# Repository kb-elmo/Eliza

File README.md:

# Eliza

[![CC BY-NC-SA 4.0][cc-by-nc-sa-shield]][cc-by-nc-sa]

### A seamless, gasketmounted 12u 40% alice-style ergo keyboard

<!---->

### This board is still in the testing prototype phase. 
#### Use the files at your own risk.

---

[STEP files for the case](case/)

[KiCAD PCB files](pcb/)

[Gerbers for PCB production](pcb/gerbers/)

[JLCPCB BOM](pcb/fab/Eliza_bom_jlc.csv)

[JLCPCB CPL](pcb/fab/Eliza_cpl_jlc.csv)

[Vial-QMK firmware](firmware/)

---

This work is licensed under a
[Creative Commons Attribution-NonCommercial-ShareAlike 4.0 International License][cc-by-nc-sa].

[![CC BY-NC-SA 4.0][cc-by-nc-sa-image]][cc-by-nc-sa]

[cc-by-nc-sa]: http://creativecommons.org/licenses/by-nc-sa/4.0/
[cc-by-nc-sa-image]: https://licensebuttons.net/l/by-nc-sa/4.0/88x31.png
[cc-by-nc-sa-shield]: https://img.shields.io/badge/License-CC%20BY--NC--SA%204.0-lightgrey.svg

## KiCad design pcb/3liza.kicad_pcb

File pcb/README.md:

# Eliza PCB

### Features

- Powered by an Atmega32u2
- Basic ESD and overvoltage protection
- Centered USB type-C port for a detachable cable
- Fully programmable using [QMK](https://qmk.fm) and [Vial](https://get.vial.today)

---

### Supported layouts

---

### Preview

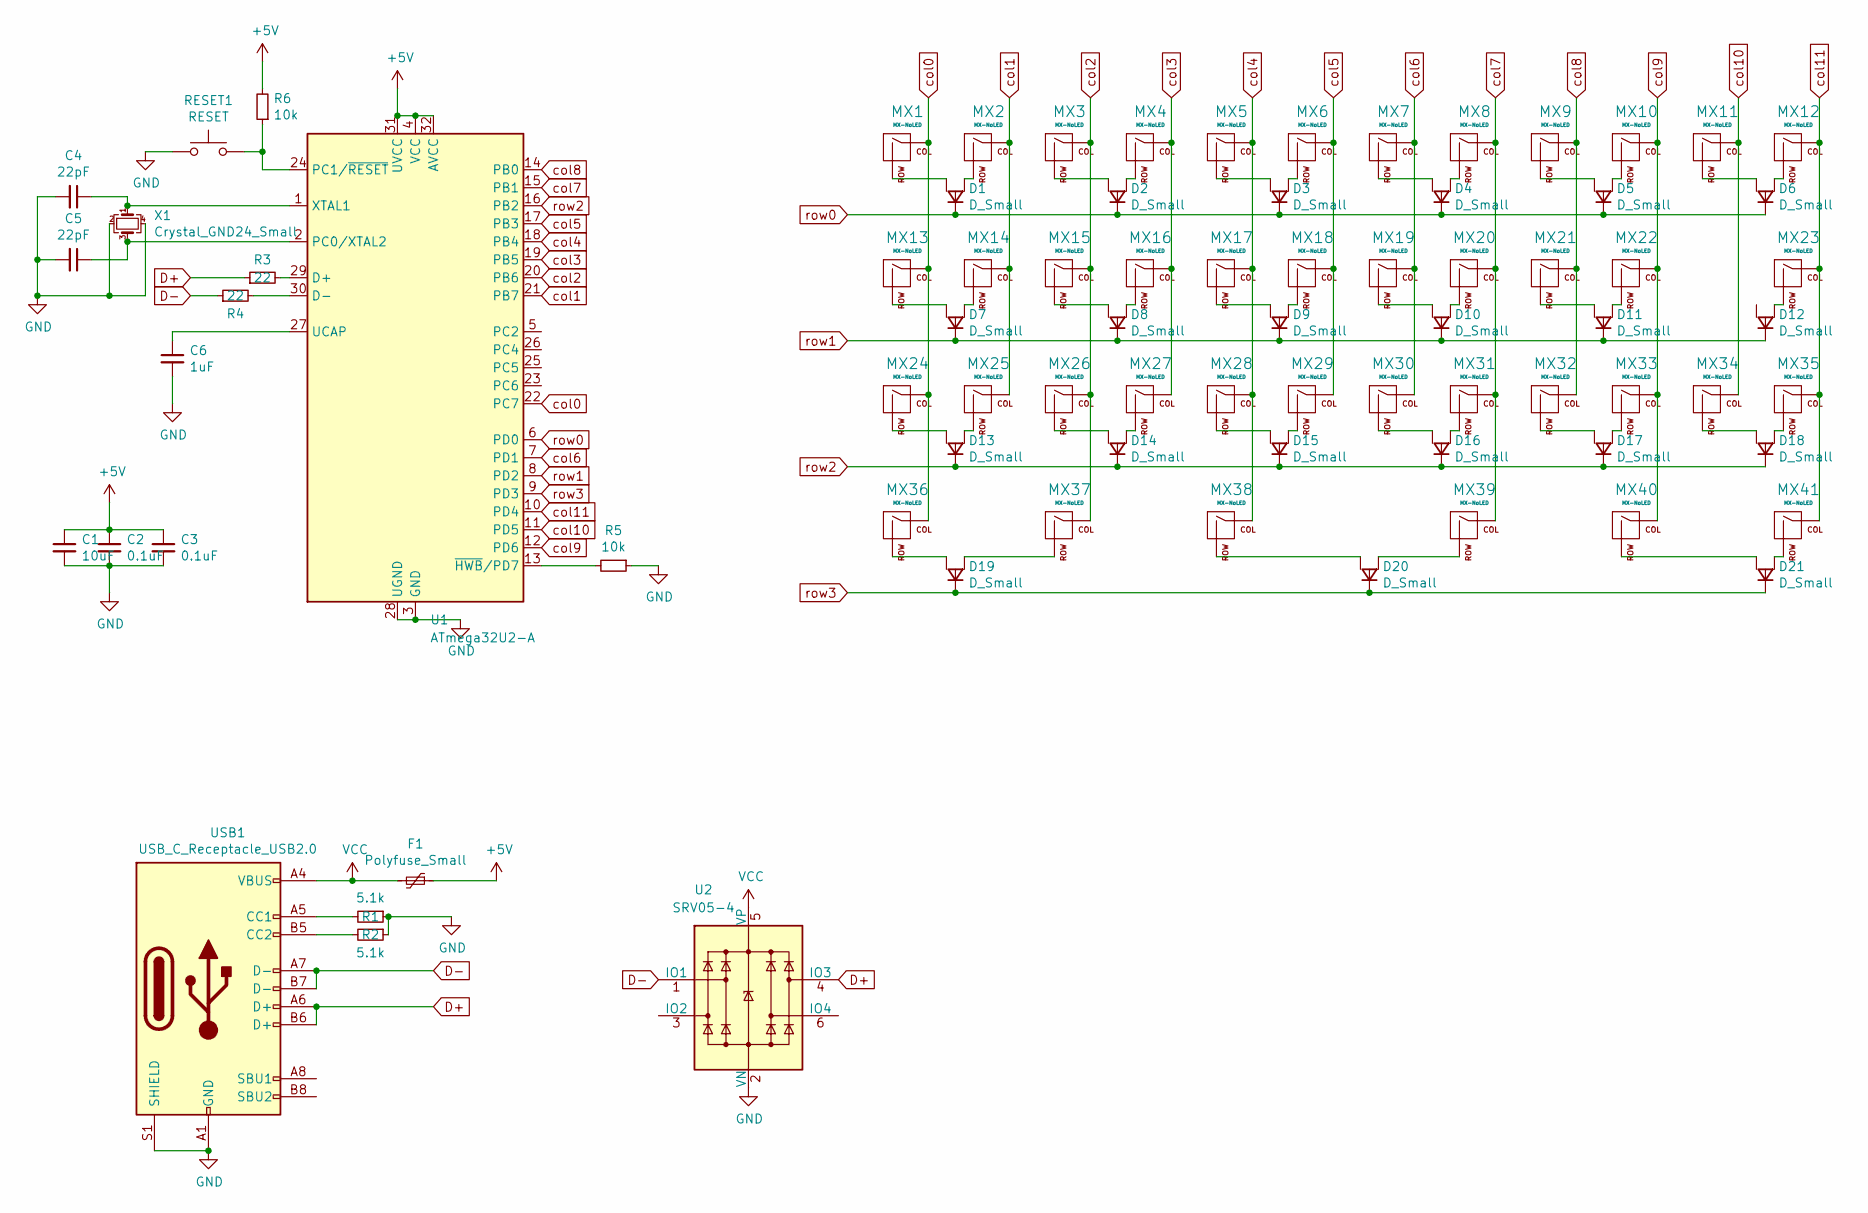
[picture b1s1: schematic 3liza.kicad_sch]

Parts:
C1: 10uF; C_0805_2012Metric; LCSC C91245
C2, C3: 0.1uF; C_0805_2012Metric; LCSC C49678
C4, C5: 22pF; C_0805_2012Metric; LCSC C1804
C6: 1uF; C_0805_2012Metric; LCSC C24123
D1, D2, D3, D4, D5, D6, D7, D8, D9, D10, D11, D12, D13, D14, D15, D16, D17, D18, D19, D20, D21: D_Small; D_SOT-23_ANK_norm; LCSC C68978
F1: Polyfuse_Small; Fuse_1206_3216Metric; LCSC C69688
MX1, MX2, MX3, MX4, MX5, MX6, MX7, MX8, MX9, MX10, MX11, MX12, MX13, MX14, MX15, MX16, MX17, MX18, MX19, MX20, MX21, MX22, MX23, MX24, MX25, MX26, MX27, MX28, MX29, MX30, MX31, MX32, MX33, MX34, MX35, MX36, MX37, MX40, MX41: MX-NoLED; MXOnly-1U-NoLED
MX38: MX-NoLED; MXOnly-2.75U-ReversedStabilizers-NoLED
MX39: MX-NoLED; MXOnly-2.25U-ReversedStabilizers-NoLED
R1, R2: 5.1k; R_0805_2012Metric; LCSC C27834
R3, R4: 22; R_0805_2012Metric; LCSC C17561
R5, R6: 10k; R_0805_2012Metric; LCSC C17414
RESET1: RESET; PinHeader_1x02_P2.54mm_Vertical
U1: ATmega32U2-A; TQFP-32_7x7mm_P0.8mm; LCSC C618733
U2: SRV05-4; SOT-23-6; LCSC C85364
USB1: USB_C_Receptacle_USB2.0; USB_C_Receptacle_HRO_TYPE-C-31-M-12; LCSC C165948
X1: Crystal_GND24_Small; Crystal_SMD_3225-4Pin_3.2x2.5mm; LCSC C13738

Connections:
+5V: C1.1, C2.1, C3.1, F1.1, R6.2, U1.4 (VCC), U1.31 (UVCC), U1.32 (AVCC)
D+: R3.1, U2.4 (IO3), USB1.A6 (D+), USB1.B6 (D+)
D-: R4.1, U2.1 (IO1), USB1.A7 (D-), USB1.B7 (D-)
GND: C1.2, C2.2, C3.2, C4.2, C5.2, C6.2, R1.1, R2.1, R5.1, RESET1.1, U1.3 (GND), U1.28 (UGND), U2.2 (VN), USB1.A1 (GND), USB1.A12 (GND), USB1.B1 (GND), USB1.B12 (GND), USB1.S1 (SHIELD), X1.2, X1.4; also elsewhere on the board
unnamed: C4.1, U1.1 (XTAL1), X1.1
unnamed: C5.1, U1.2 (PC0/XTAL2), X1.3
unnamed: C6.1, U1.27 (UCAP)
unnamed: D1.2 (A1), MX1.2 (ROW)
unnamed: D1.3 (A2), MX2.2 (ROW)
unnamed: D2.2 (A1), MX3.2 (ROW)
unnamed: D2.3 (A2), MX4.2 (ROW)
unnamed: D3.2 (A1), MX5.2 (ROW)
unnamed: D3.3 (A2), MX6.2 (ROW)
unnamed: D4.2 (A1), MX7.2 (ROW)
unnamed: D4.3 (A2), MX8.2 (ROW)
unnamed: D5.2 (A1), MX9.2 (ROW)
unnamed: D5.3 (A2), MX10.2 (ROW)
unnamed: D6.2 (A1), MX11.2 (ROW)
unnamed: D6.3 (A2), MX12.2 (ROW)
unnamed: D7.2 (A1), MX13.2 (ROW)
unnamed: D7.3 (A2), MX14.2 (ROW)
unnamed: D8.2 (A1), MX15.2 (ROW)
unnamed: D8.3 (A2), MX16.2 (ROW)
unnamed: D9.2 (A1), MX17.2 (ROW)
unnamed: D9.3 (A2), MX18.2 (ROW)
unnamed: D10.2 (A1), MX19.2 (ROW)
unnamed: D10.3 (A2), MX20.2 (ROW)
unnamed: D11.2 (A1), MX21.2 (ROW)
unnamed: D11.3 (A2), MX22.2 (ROW)
unnamed: D12.3 (A2), MX23.2 (ROW)
unnamed: D13.2 (A1), MX24.2 (ROW)
unnamed: D13.3 (A2), MX25.2 (ROW)
unnamed: D14.2 (A1), MX26.2 (ROW)
unnamed: D14.3 (A2), MX27.2 (ROW)
unnamed: D15.2 (A1), MX28.2 (ROW)
unnamed: D15.3 (A2), MX29.2 (ROW)
unnamed: D16.2 (A1), MX30.2 (ROW)
unnamed: D16.3 (A2), MX31.2 (ROW)
unnamed: D17.2 (A1), MX32.2 (ROW)
unnamed: D17.3 (A2), MX33.2 (ROW)
unnamed: D18.2 (A1), MX34.2 (ROW)
unnamed: D18.3 (A2), MX35.2 (ROW)
unnamed: D19.2 (A1), MX36.2 (ROW)
unnamed: D19.3 (A2), MX37.2 (ROW)
unnamed: D20.2 (A1), MX38.2 (ROW)
unnamed: D20.3 (A2), MX39.2 (ROW)
unnamed: D21.2 (A1), MX40.2 (ROW)
unnamed: D21.3 (A2), MX41.2 (ROW)
unnamed: R1.2, USB1.A5 (CC1)
unnamed: R2.2, USB1.B5 (CC2)
unnamed: R3.2, U1.29 (D+)
unnamed: R4.2, U1.30 (D-)
unnamed: R5.2, U1.13 (~HWB/PD7)
unnamed 53: R6.1, RESET1.2, U1.24 (PC1/~RESET); also elsewhere on the board
VCC: F1.2, U2.5 (VP), USB1.A4 (VBUS), USB1.A9 (VBUS), USB1.B4 (VBUS), USB1.B9 (VBUS)
col0: MX1.1 (COL), MX13.1 (COL), MX24.1 (COL), MX36.1 (COL), U1.22 (PC7)
col1: MX2.1 (COL), MX14.1 (COL), MX25.1 (COL), U1.21 (PB7)
col2: MX3.1 (COL), MX15.1 (COL), MX26.1 (COL), MX37.1 (COL), U1.20 (PB6)
col3: MX4.1 (COL), MX16.1 (COL), MX27.1 (COL), U1.19 (PB5)
col4: MX5.1 (COL), MX17.1 (COL), MX28.1 (COL), MX38.1 (COL), U1.18 (PB4)
col5: MX6.1 (COL), MX18.1 (COL), MX29.1 (COL), U1.17 (PB3)
col6: MX7.1 (COL), MX19.1 (COL), MX30.1 (COL), U1.7 (PD1)
col7: MX8.1 (COL), MX20.1 (COL), MX31.1 (COL), MX39.1 (COL), U1.15 (PB1)
col8: MX9.1 (COL), MX21.1 (COL), MX32.1 (COL), U1.14 (PB0)
col9: MX10.1 (COL), MX22.1 (COL), MX33.1 (COL), MX40.1 (COL), U1.12 (PD6)
col10: MX11.1 (COL), MX34.1 (COL), U1.11 (PD5)
col11: MX12.1 (COL), MX23.1 (COL), MX35.1 (COL), MX41.1 (COL), U1.10 (PD4)
row0: D1.1 (K), D2.1 (K), D3.1 (K), D4.1 (K), D5.1 (K), D6.1 (K), U1.6 (PD0)
row1: D7.1 (K), D8.1 (K), D9.1 (K), D10.1 (K), D11.1 (K), D12.1 (K), U1.8 (PD2)
row2: D13.1 (K), D14.1 (K), D15.1 (K), D16.1 (K), D17.1 (K), D18.1 (K), U1.16 (PB2)
row3: D19.1 (K), D20.1 (K), D21.1 (K), U1.9 (PD3)

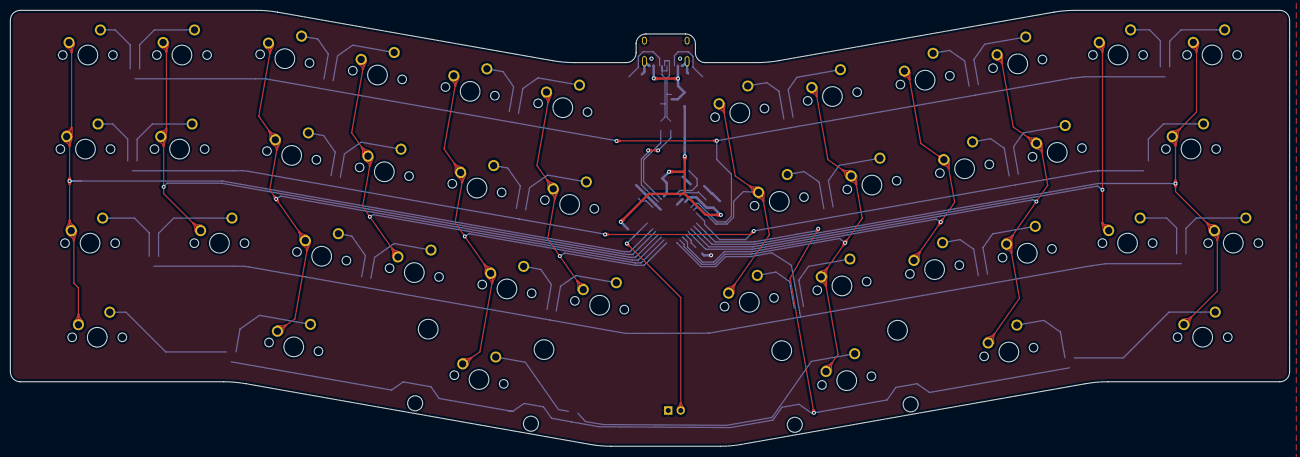
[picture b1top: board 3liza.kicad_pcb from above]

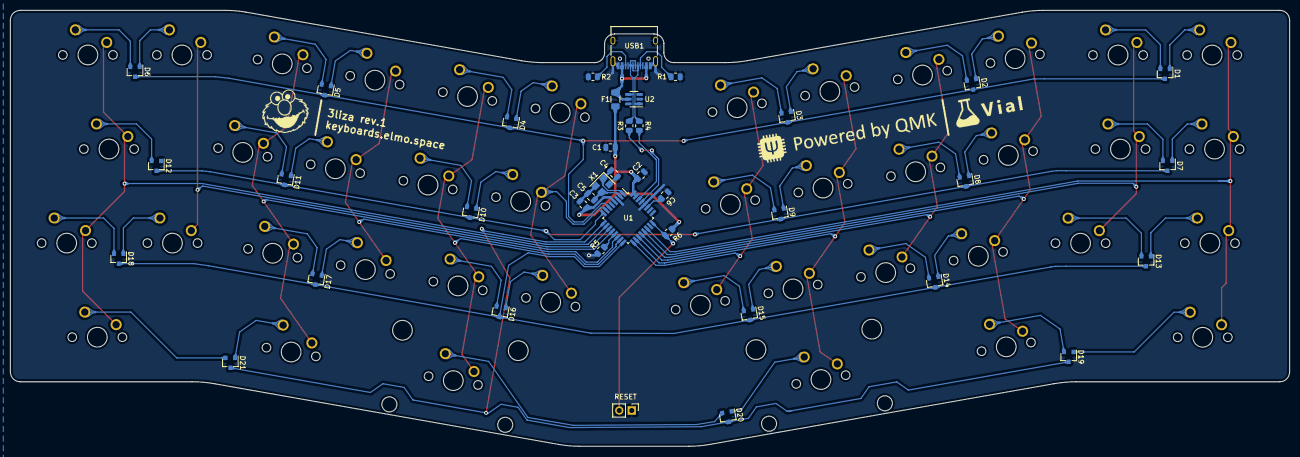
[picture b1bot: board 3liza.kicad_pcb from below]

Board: 2 copper layers, 259.0 x 88.3 mm, 80 parts (39 on the bottom side), 71 nets.

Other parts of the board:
RESET: RESET; PinHeader_1x02_P2.54mm_Vertical

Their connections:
GND: RESET.1; also elsewhere on the board
unnamed 53: RESET.2; also elsewhere on the board

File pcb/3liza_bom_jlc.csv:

"Comment","Designator","Footprint","LCSC Part #"
"10uF","C1","C_0805_2012Metric","C91245"
"0.1uF","C2,C3","C_0805_2012Metric","C49678"
"22pF","C4,C5","C_0805_2012Metric","C1804"
"1uF","C6","C_0805_2012Metric","C24123"
"D_Small","D1,D2,D3,D4,D5,D6,D7,D8,D9,D10,D11,D12,D13,D14,D15,D16,D17,D18,D19,D20,D21","D_SOT-23_ANK_norm","C68978"
"Polyfuse_Small","F1","Fuse_1206_3216Metric","C69688"
"5.1k","R1,R2","R_0805_2012Metric","C27834"
"22","R3,R4","R_0805_2012Metric","C17561"
"10k","R5,R6","R_0805_2012Metric","C17414"
"ATmega32U2-A","U1","TQFP-32_7x7mm_P0.8mm","C618733"
"SRV05-4","U2","SOT-23-6","C85364"
"USB_C_Receptacle_USB2.0","USB1","USB_C_Receptacle_HRO_TYPE-C-31-M-12","C165948"
"Crystal_GND24_Small","X1","Crystal_SMD_3225-4Pin_3.2x2.5mm","C13738"

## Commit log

2022-06-01 move files
2022-06-01 add case files
2024-02-21 fix pcb renders
2024-02-21 remove pcb test files
2024-02-24 Rename and small updates
